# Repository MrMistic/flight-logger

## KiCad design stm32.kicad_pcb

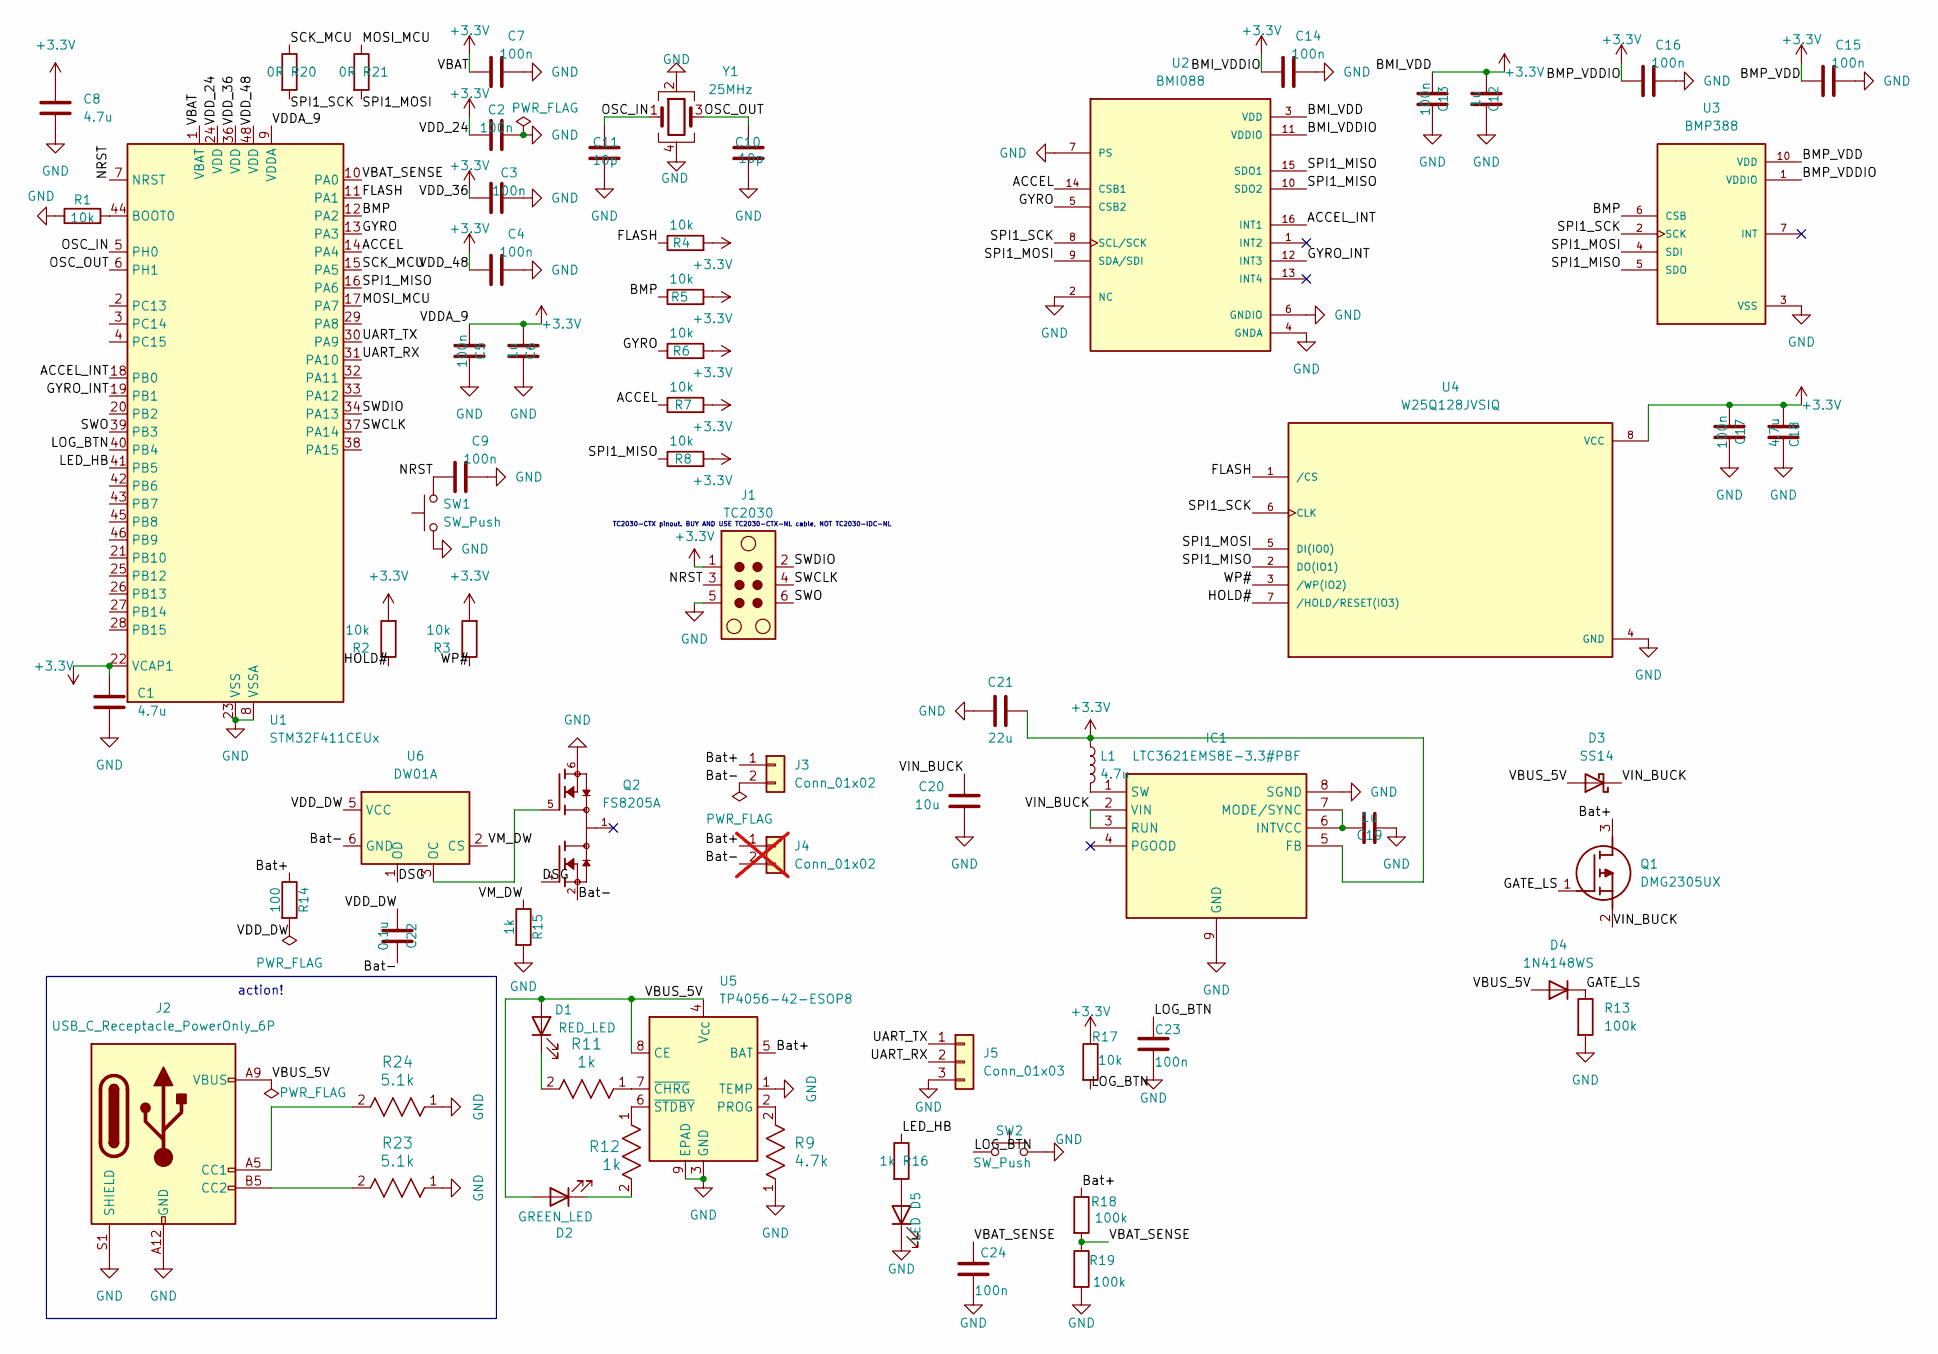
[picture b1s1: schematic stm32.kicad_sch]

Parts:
C1, C8, C18: 4.7u; C_0603_1608Metric
C2, C3, C4, C5, C7, C9, C13, C14, C15, C16, C17, C23, C24: 100n; C_0402_1005Metric
C6, C12, C19: 1u; C_0402_1005Metric
C10, C11: 10p; C_0402_1005Metric
C20: 10u; C_0603_1608Metric
C21: 22u; C_0603_1608Metric
C22: 0.1u; C_0402_1005Metric
D1: RED_LED; LED_Kingbright_KPBD-3224
D2: GREEN_LED; LED_Kingbright_KPBD-3224
D3: SS14; D_SMA
D4: 1N4148WS; D_SOD-323
D5: LED; LED_0603_1608Metric
IC1: LTC3621EMS8E-3.3#PBF; Mouser Part Number 584-C3621EMS8E-3.3PF
J1: TC2030; Tag-Connect_TC2030-IDC-NL_2x03_P1.27mm_Vertical
J2: USB_C_Receptacle_PowerOnly_6P; USB_C_Receptacle_GCT_USB4125-xx-x_6P_TopMnt_Horizontal
J3: Conn_01x02; JST_PH_S2B-PH-SM4-TB_1x02-1MP_P2.00mm_Horizontal
J4: Conn_01x02; PinHeader_1x02_P2.54mm_Vertical; not fitted
J5: Conn_01x03; PinHeader_1x03_P2.54mm_Vertical
L1: 4.7u; L_Coilcraft_XxL4020
Q1: DMG2305UX; Manufacturer_Part_Number DMG2305UX; Mouser Part Number N/A
Q2: FS8205A; PARTREV 1.7
R1, R2, R3, R4, R5, R6, R7, R8, R17: 10k; R_0402_1005Metric
R9: 4.7k; R_0402_1005Metric
R11, R12, R15, R16: 1k; R_0402_1005Metric
R13, R18, R19: 100k; R_0402_1005Metric
R14: 100; R_0402_1005Metric
R20, R21: 0R; R_0402_1005Metric
R23, R24: 5.1k; R_0402_1005Metric
SW1: SW_Push; SW_SPST_B3S-1000
SW2: SW_Push; SW_SPST_CK_RS282G05A3
U1: STM32F411CEUx; QFN-48-1EP_7x7mm_P0.5mm_EP5.6x5.6mm
U2: BMI088
U3: BMP388; PARTREV 1.7
U4: W25Q128JVSIQ; W25Q128; PARTREV I
U5: TP4056-42-ESOP8; SOIC-8-1EP_3.9x4.9mm_P1.27mm_EP2.41x3.3mm_ThermalVias
U6: DW01A; SOT-23-6
Y1: 25MHz; Crystal_SMD_3225-4Pin_3.2x2.5mm

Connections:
+3.3V: C1.1, C2.1, C3.1, C4.1, C5.1, C6.1, C7.1, C8.1, C12.1, C13.1, C14.1, C15.1, C16.1, C17.1, C18.1, C21.2, IC1.5 (FB), J1.1, L1.1, R2.2, R3.2, R4.2, R5.2, R6.2, R7.2, R8.2, R17.1, U1.1 (VBAT), U1.9 (VDDA), U1.22 (VCAP1), U1.24 (VDD), U1.36 (VDD), U1.48 (VDD), U2.3 (VDD), U2.11 (VDDIO), U3.1 (VDDIO), U3.10 (VDD), U4.8 (VCC)
/ACCEL: R7.1, U1.14 (PA4), U2.14 (CSB1)
/ACCEL_INT: U1.18 (PB0), U2.16 (INT1)
/BMP: R5.1, U1.12 (PA2), U3.6 (CSB)
/Bat+: J3.1, J4.1, Q1.3 (D), R14.1, R18.1, U5.5 (BAT)
/Bat-: C22.2, J3.2, J4.2, Q2.2, Q2.3, U6.6 (GND)
/DSG: Q2.4, U6.1 (OD)
/FLASH: R4.1, U1.11 (PA1), U4.1 (/CS)
/GATE_LS: D4.1 (K), Q1.1 (G), R13.1
/GYRO: R6.1, U1.13 (PA3), U2.5 (CSB2)
/GYRO_INT: U1.19 (PB1), U2.12 (INT3)
/HOLD#: R2.1, U4.7 (/HOLD/RESET(IO3))
/LED_HB: R16.1, U1.41 (PB5)
/LOG_BTN: C23.1, R17.2, SW2.1, U1.40 (PB4)
/MOSI_MCU: R21.1, U1.17 (PA7)
/NRST: C9.1, J1.3, SW1.2, U1.7 (NRST)
/OSC_IN: C11.2, U1.5 (PH0), Y1.1
/OSC_OUT: C10.2, U1.6 (PH1), Y1.3
/SCK_MCU: R20.1, U1.15 (PA5)
/SPI1_MISO: R8.1, U1.16 (PA6), U2.10 (SDO2), U2.15 (SDO1), U3.5 (SDO), U4.2 (DO(IO1))
/SPI1_MOSI: R21.2, U2.9 (SDA/SDI), U3.4 (SDI), U4.5 (DI(IO0))
/SPI1_SCK: R20.2, U2.8 (SCL/SCK), U3.2 (SCK), U4.6 (CLK)
/SWCLK: J1.4, U1.37 (PA14)
/SWDIO: J1.2, U1.34 (PA13)
/SWO: J1.6, U1.39 (PB3)
/UART_RX: J5.2, U1.31 (PA10)
/UART_TX: J5.1, U1.30 (PA9)
/VBAT_SENSE: C24.1, R18.2, R19.1, U1.10 (PA0)
/VBUS_5V: D1.2 (A), D2.2 (A), D3.2 (A), D4.2 (A), J2.A9 (VBUS), J2.B9 (VBUS), U5.4 (V_{CC}), U5.8 (CE)
/VDD_DW: C22.1, R14.2, U6.5 (VCC)
/VIN_BUCK: C20.1, D3.1 (K), IC1.2 (VIN), IC1.3 (RUN), Q1.2 (S)
/VM_DW: R15.1, U6.2 (CS)
/WP#: R3.1, U4.3 (/WP(IO2))
GND: C1.2, C2.2, C3.2, C4.2, C5.2, C6.2, C7.2, C8.2, C9.2, C10.1, C11.1, C12.2, C13.2, C14.2, C15.2, C16.2, C17.2, C18.2, C19.2, C20.2, C21.1, C23.2, C24.2, D5.1 (K), IC1.8 (SGND), IC1.9 (GND), J1.5, J2.A12 (GND), J2.B12 (GND), J2.S1 (SHIELD), J5.3, Q2.6, Q2.7, R1.1, R9.1, R13.2, R15.2, R19.2, R23.1, R24.1, SW1.1, SW2.2, U1.8 (VSSA), U1.23 (VSS), U1.35 (VSS), U1.47 (VSS), U1.49 (VSS), U2.2 (NC), U2.4 (GNDA), U2.6 (GNDIO), U2.7 (PS), U3.3 (VSS), U3.8 (VSS), U3.9 (VSS), U4.4 (GND), U5.1 (TEMP), U5.3 (GND), U5.9 (EPAD), Y1.2, Y1.4; also elsewhere on the board
unnamed: D1.1 (K), R11.2
unnamed: D2.1 (K), R12.2
unnamed: D5.2 (A), R16.2
unnamed: C19.1, IC1.6 (INTVCC), IC1.7 (MODE/SYNC)
unnamed: IC1.1 (SW), L1.2
unnamed: J2.A5 (CC1), R24.2
unnamed: J2.B5 (CC2), R23.2
unnamed: Q2.1, Q2.8
unnamed: R1.2, U1.44 (BOOT0)
unnamed: R9.2, U5.2 (PROG)
unnamed: R11.1, U5.7 (~CHRG)
unnamed: R12.1, U5.6 (~STDBY)
unnamed: Q2.5, U6.3 (OC)

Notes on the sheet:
TC2030-CTX pinout. BUY AND USE TC2030-CTX-NL cable, NOT TC2030-IDC-NL
action!

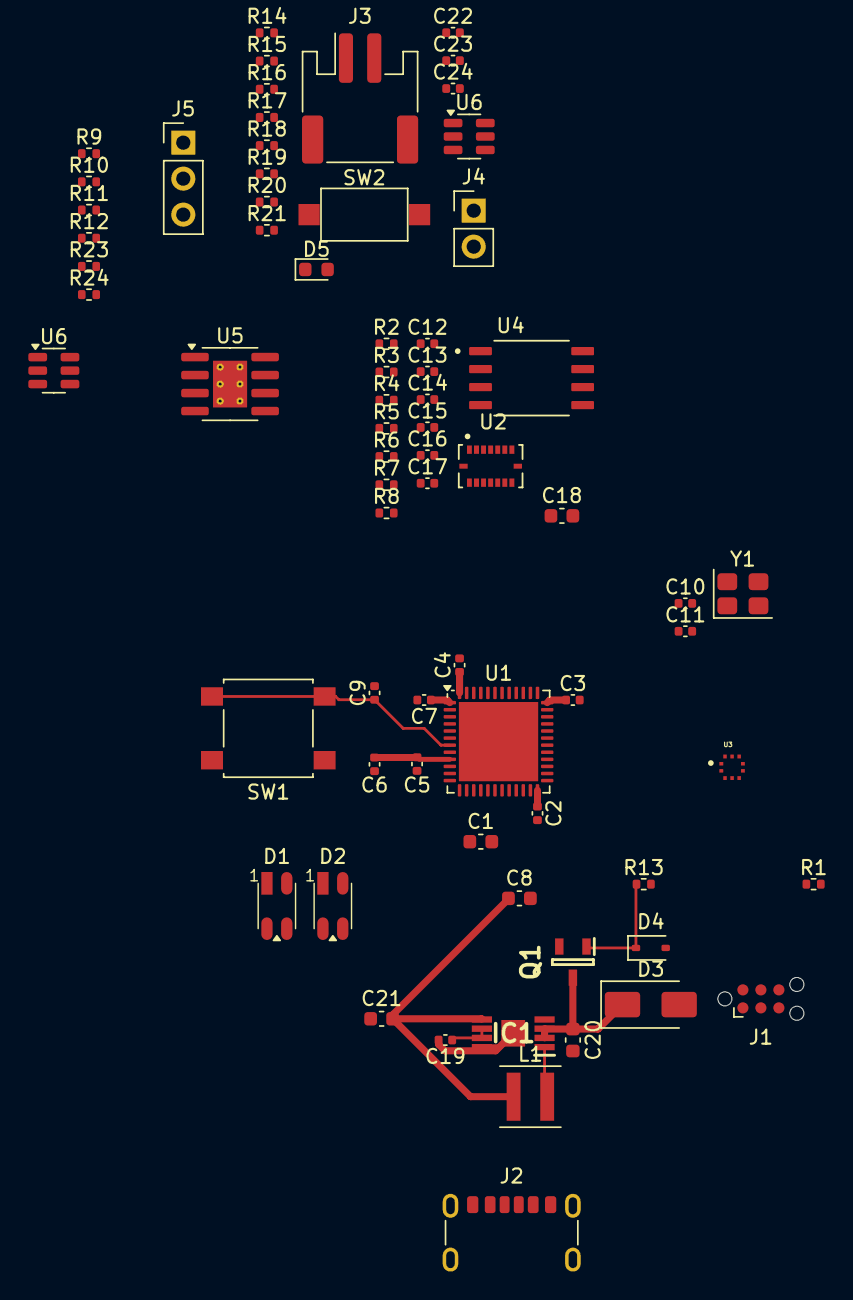
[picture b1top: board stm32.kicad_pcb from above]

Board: 2 copper layers, 70 parts (0 on the bottom side), 44 nets.

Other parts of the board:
R10: 10k; R_0402_1005Metric
U6#2: AP63203WU; TSOT-23-6

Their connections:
GND: R10.1; also elsewhere on the board

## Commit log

2026-06-05 Initial commit: project skeleton
2026-06-05 Initial commit: STM32 core + decoupling + crystal section
2026-06-05 Clean up: remove KiCAD auto-generated files from tracking
2026-06-10 SWD: complete Tag-Connect TC2030 wiring with SWO + VTref cap
2026-06-10 fixing crystal
2026-06-16 SPI bus: MCU-side wiring (SPI1 = PA5/6/7, CS = PA1-4, INT = PB0/1, pull-ups on CS+MISO)
2026-06-16 SPI section: place BMI088, BMP388, W25Q128 symbols + decoupling + HOLD/WP pull-ups
2026-06-16 Power: TP4056 charger (Iprog=255mA via 4.7k PROG, status LEDs, NTC disabled)
2026-06-17 small update
2026-06-17 replaced buck
2026-06-18 fleshed out buck
2026-06-24 next steps
2026-06-26 Fix DW01A/FS8205A protection wiring and load-share P-FET orientation
    - DW01A: VSS->Bat- (cell neg), VM->1k->GND sense, VDD<-100R<-Bat+ with 0.1uF bypass
    - Correct gate drive: OD->FS8205 G1, OC->FS8205 G2; remove G1 no-connect
    - Float FS8205 common drain (was tied to BAT-)
    - Swap load-share P-FET S/D so body diode conducts Bat+->VIN_BUCK
    - Merge BAT_OUT into Bat+; rename cell-negative net to Bat-
    - Add buck input/output caps; gitignore datasheets and local backup
2026-06-26 added lipo connector
2026-06-26 Mark J4 battery solder-header as DNP (JST-PH J3 is primary)
2026-06-27 Connect HSE crystal to MCU; add LED, logging button, battery sense, UART header
    - Wire crystal OSC_IN/OSC_OUT to STM32 PH0/PH1 (was floating)
    - Status LED (D5+R16 1k) on PB5, active-high
    - Logging button (SW2) on PB4 with 10k pull-up (R17) + 100n debounce (C23)
    - Battery sense divider (R18/R19 100k, C24 100n) Bat+ -> PA0 (ADC1_IN0)
    - Wire existing UART header J5: PA9 TX, PA10 RX, GND
2026-06-27 Add 0R resistors for safety
2026-06-27 added ERC
2026-06-27 Resolve ERC: fix +3.3V power flag, FS8205 drain no-connect
2026-06-28 Assign J5 UART header footprint; import netlist to PCB for layout
